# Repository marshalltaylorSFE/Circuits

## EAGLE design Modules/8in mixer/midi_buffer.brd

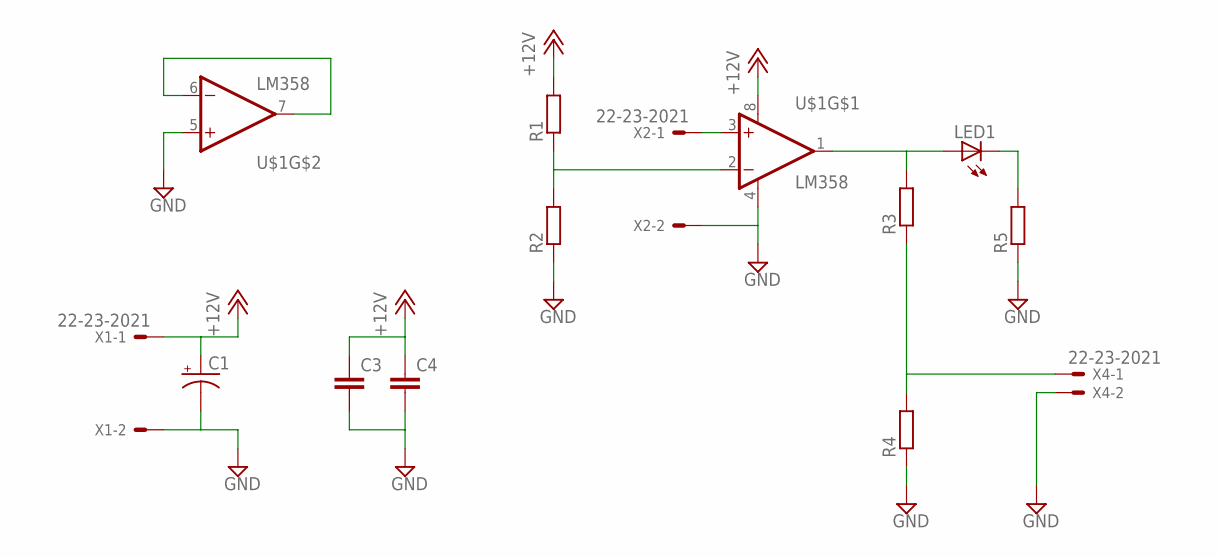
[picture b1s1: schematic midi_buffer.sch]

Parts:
C1: CPOL-USSMCE; SMC_E
C3, C4: C-EUC0603K; C0603K
LED1: LEDSML0805; SML0805
R1, R2, R3, R4, R5: R-EU_R0603; R0603
U$1: LM358; SO08
X1, X2, X4: 22-23-2021

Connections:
+12V: C1.+, C3.1, C4.1, R1.2, U$1.8 (V+), X1.1
GND: C1.-, C3.2, C4.2, R2.1, R4.1, R5.1, U$1.4 (V-), U$1.5 (+IN), X1.2, X2.2, X4.2
unnamed: R3.1, R4.2, X4.1
unnamed: LED1.C, R5.2
unnamed: LED1.A, R3.2, U$1.1 (OUT)
unnamed: R1.1, R2.2, U$1.2 (-IN)
unnamed: U$1.3 (+IN), X2.1
unnamed: U$1.6 (-IN), U$1.7 (OUT)

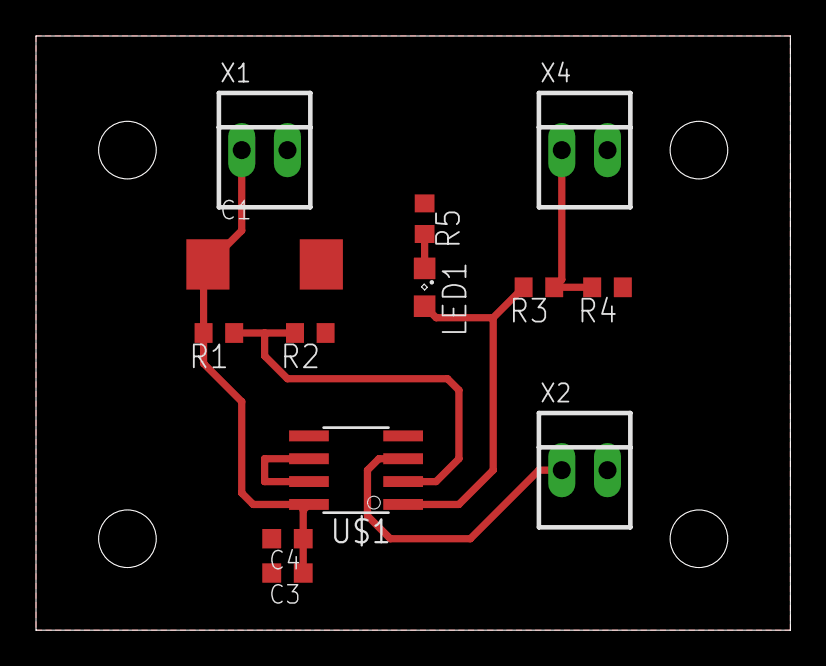
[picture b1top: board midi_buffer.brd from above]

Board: 2 copper layers, 41.9 x 33.0 mm, 13 parts (0 on the bottom side), 8 nets.

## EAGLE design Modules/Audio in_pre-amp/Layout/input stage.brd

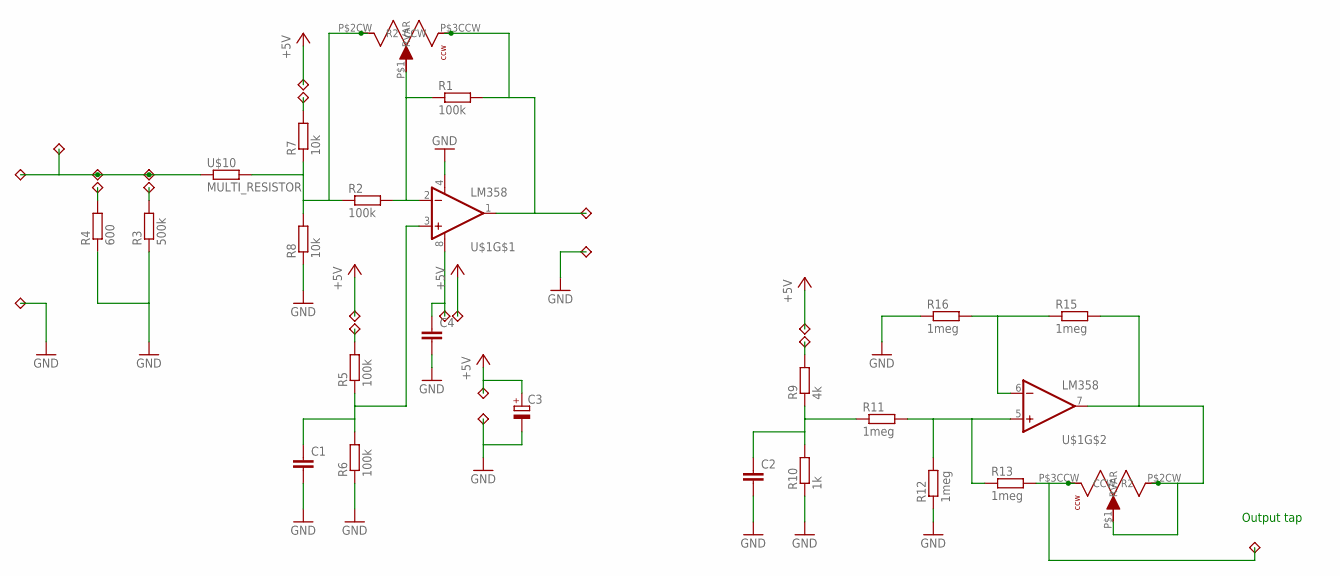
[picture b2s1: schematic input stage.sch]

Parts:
C1, C2, C4: C-EUC0603; C0603
C3: CPOL-EUC/6032-28R; C/6032-28R
R1, R2, R5, R6: 100k; R0603
R3: 500k; R0603
R4: 600; R0603
R7, R8: 10k; R0603
R9: 4k; R0603
R10: 1k; R0603
R11, R12, R13, R15, R16: 1meg; R0603
U$1: LM358; SO08
U$2, U$3, U$4, U$5, U$6, U$7, U$8, U$9, U$11, U$12, U$13, U$14: 1PIN; THUMBNAIL
U$10: MULTI_RESISTOR; MULTI_PAD
U$15, U$24: SMD-POT; POT_PADS
U$16, U$17, U$18, U$19, U$20, U$21, U$22, U$23: 1PIN_SM; THUMBNAIL_SM

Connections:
+5V: C3.+, U$2.P$1, U$17.P$1, U$19.P$1, U$21.P$1, U$23.P$1
GND: C1.2, C2.2, C3.-, C4.2, R3.1, R4.1, R6.1, R8.1, R10.1, R12.1, R16.1, U$1.4 (V-), U$3.P$1, U$8.P$1, U$9.P$1
unnamed: C1.1, R5.1, R6.2, U$1.3 (+IN)
unnamed: R1.1, R2.2, U$1.2 (-IN), U$24.P$1 (RVAR)
unnamed: U$5.P$1, U$6.P$1, U$10.1, U$12.P$1, U$13.P$1
unnamed: R1.2, U$1.1 (OUT), U$4.P$1, U$24.P$3CCW (CCW)
unnamed: R4.2, U$7.P$1
unnamed: R2.1, R7.1, R8.2, U$10.2, U$24.P$2CW (R2)
unnamed: R3.2, U$11.P$1
unnamed: C2.1, R9.1, R10.2, R11.1
unnamed: R15.1, R16.2, U$1.6 (-IN)
unnamed: R15.2, U$1.7 (OUT), U$15.P$1 (RVAR), U$15.P$2CW (R2)
unnamed: R13.2, U$14.P$1, U$15.P$3CCW (CCW)
unnamed: R11.2, R12.2, R13.1, U$1.5 (+IN)
unnamed: R9.2, U$16.P$1
unnamed: R7.2, U$18.P$1
unnamed: R5.2, U$20.P$1
unnamed: C4.1, U$1.8 (V+), U$22.P$1

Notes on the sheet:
Output tap

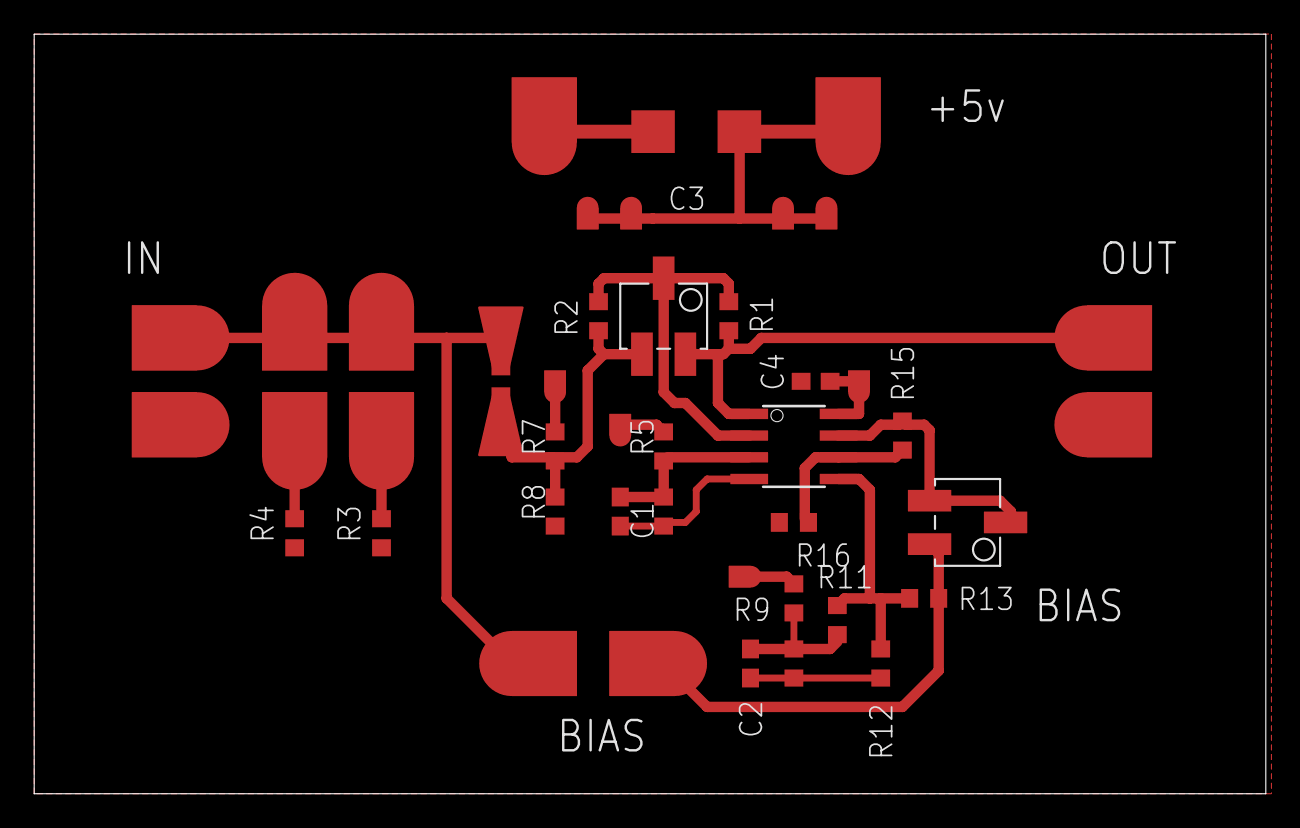
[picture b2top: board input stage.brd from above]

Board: 2 copper layers, 72.1 x 44.4 mm, 43 parts (0 on the bottom side), 18 nets.

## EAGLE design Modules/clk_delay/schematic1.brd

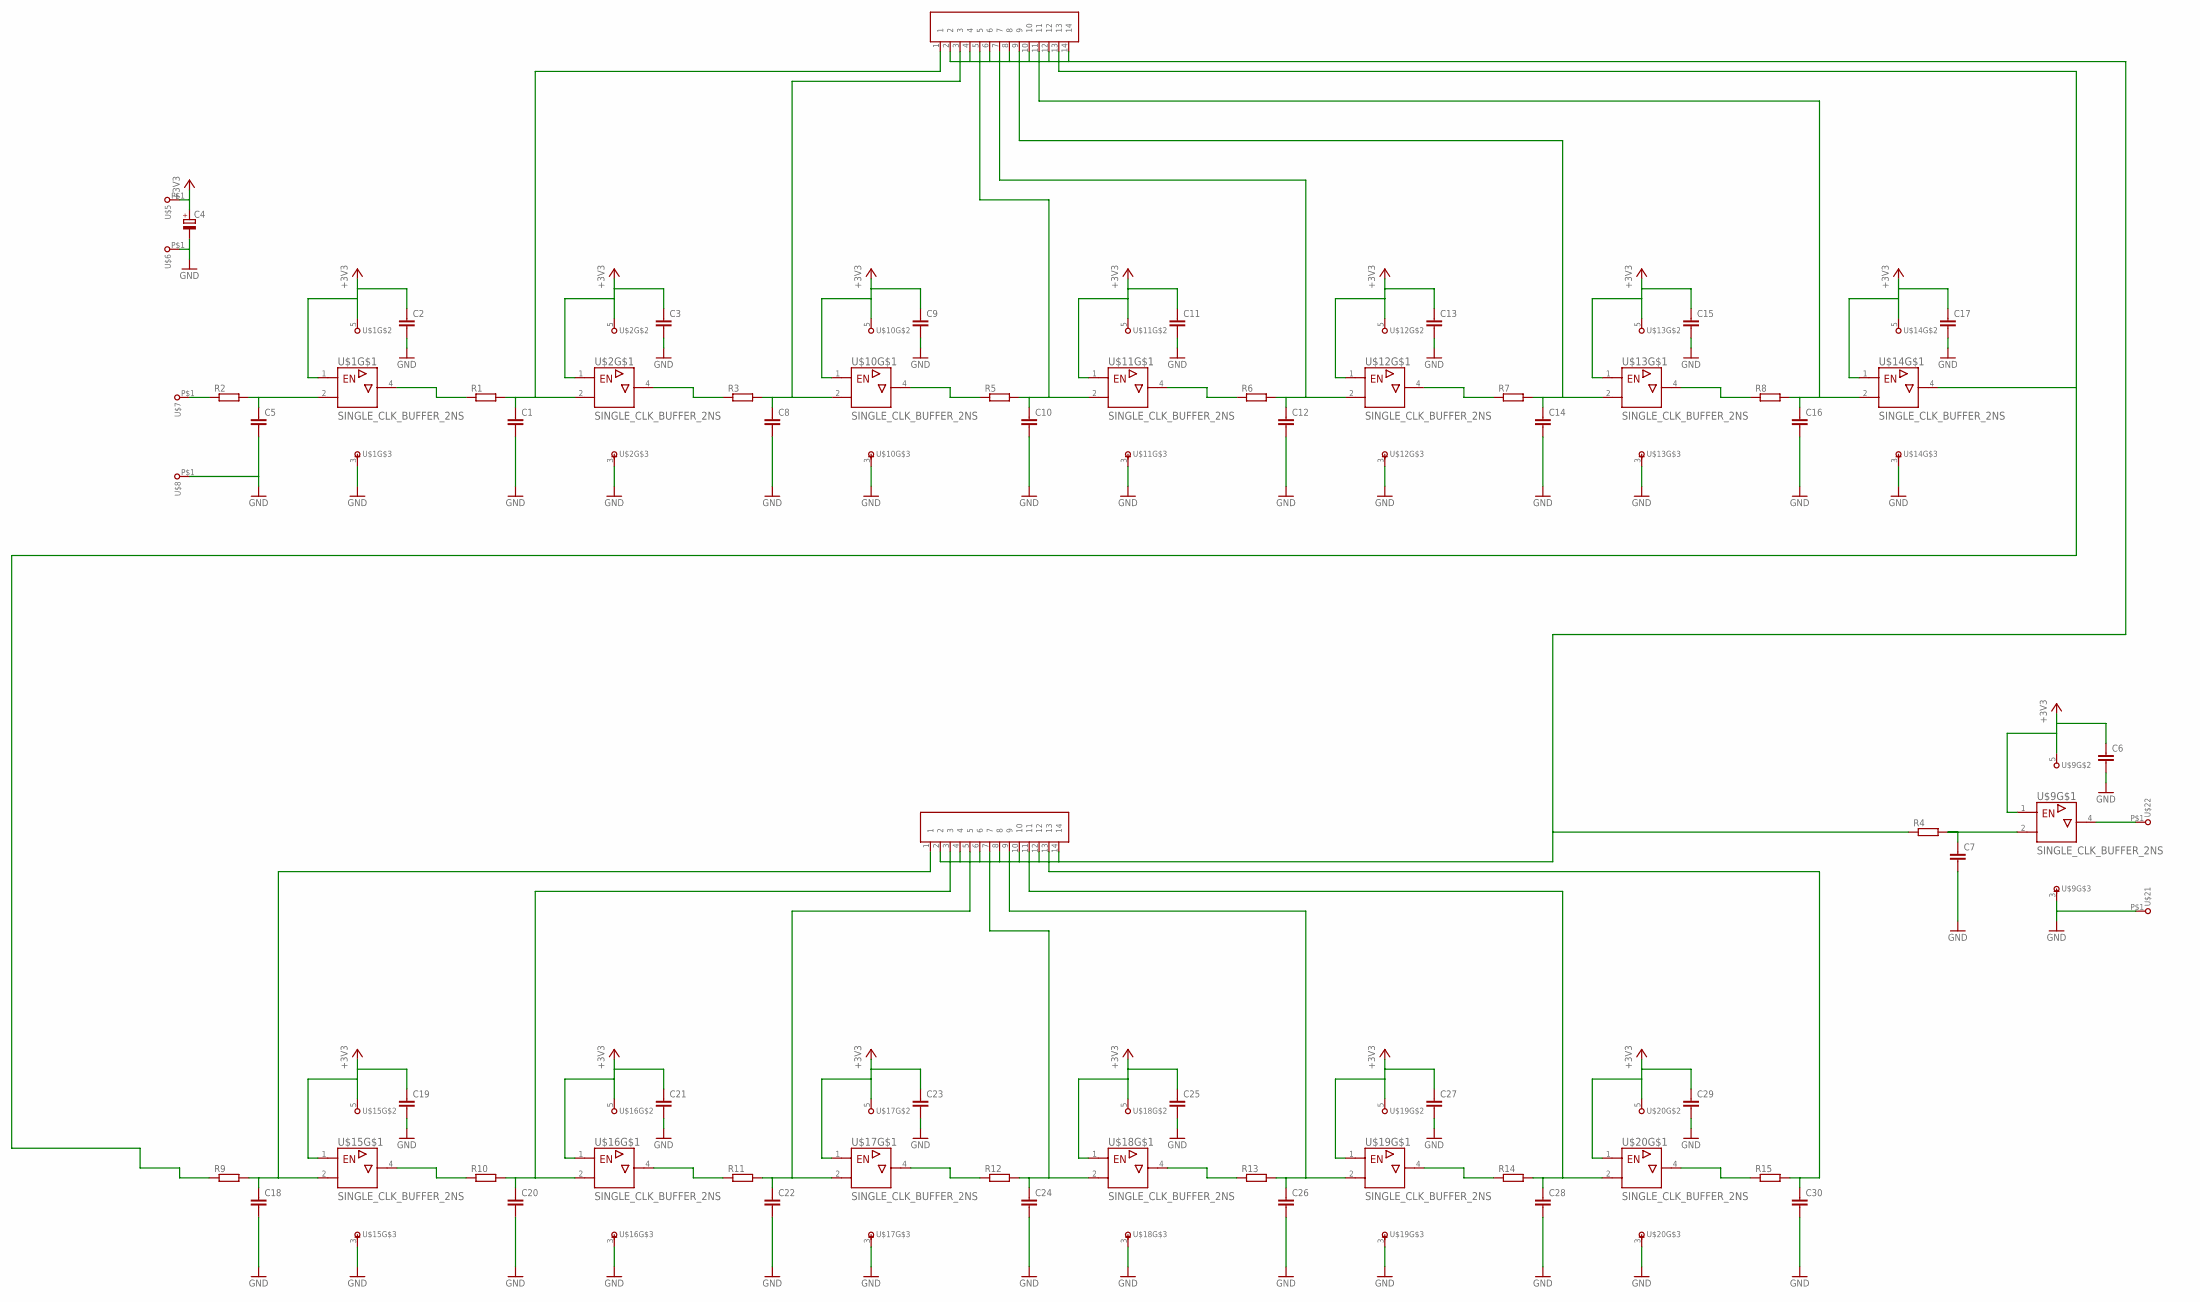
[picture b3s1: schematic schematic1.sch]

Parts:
C1, C5, C7, C8, C10, C12, C14, C16, C18, C20, C22, C24, C26, C28, C30: C-EUC0603; C0603
C2, C3, C6, C9, C11, C13, C15, C17, C19, C21, C23, C25, C27, C29: C-EUC0805; C0805
C4: CPOL-EUSMCD; SMC_D
R1, R2, R3, R4, R5, R6, R7, R8, R9, R10, R11, R12, R13, R14, R15: R-EU_R0603; R0603
U$1, U$2, U$9, U$10, U$11, U$12, U$13, U$14, U$15, U$16, U$17, U$18, U$19, U$20: SINGLE_CLK_BUFFER_2NS; DCK
U$3, U$4: 2X7SMD_HEADER; 2X14SMDPADS
U$5, U$6, U$7, U$8, U$21, U$22: BIGGOPAD

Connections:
+3V3: C2.1, C3.1, C4.+, C6.1, C9.1, C11.1, C13.1, C15.1, C17.1, C19.1, C21.1, C23.1, C25.1, C27.1, C29.1, U$1.1 (G), U$1.5 (+UB), U$2.1 (G), U$2.5 (+UB), U$5.P$1, U$9.1 (G), U$9.5 (+UB), U$10.1 (G), U$10.5 (+UB), U$11.1 (G), U$11.5 (+UB), U$12.1 (G), U$12.5 (+UB), U$13.1 (G), U$13.5 (+UB), U$14.1 (G), U$14.5 (+UB), U$15.1 (G), U$15.5 (+UB), U$16.1 (G), U$16.5 (+UB), U$17.1 (G), U$17.5 (+UB), U$18.1 (G), U$18.5 (+UB), U$19.1 (G), U$19.5 (+UB), U$20.1 (G), U$20.5 (+UB)
GND: C1.2, C2.2, C3.2, C4.-, C5.2, C6.2, C7.2, C8.2, C9.2, C10.2, C11.2, C12.2, C13.2, C14.2, C15.2, C16.2, C17.2, C18.2, C19.2, C20.2, C21.2, C22.2, C23.2, C24.2, C25.2, C26.2, C27.2, C28.2, C29.2, C30.2, U$1.3 (-UB), U$2.3 (-UB), U$6.P$1, U$8.P$1, U$9.3 (-UB), U$10.3 (-UB), U$11.3 (-UB), U$12.3 (-UB), U$13.3 (-UB), U$14.3 (-UB), U$15.3 (-UB), U$16.3 (-UB), U$17.3 (-UB), U$18.3 (-UB), U$19.3 (-UB), U$20.3 (-UB), U$21.P$1
unnamed: C5.1, R2.2, U$1.2 (A)
unnamed: R2.1, U$7.P$1
unnamed: C1.1, R1.2, U$2.2 (A), U$3.1
unnamed: R1.1, U$1.4 (Y)
unnamed: C7.1, R4.2, U$9.2 (A)
unnamed: R3.1, U$2.4 (Y)
unnamed: C8.1, R3.2, U$3.3, U$10.2 (A)
unnamed: C10.1, R5.2, U$3.5, U$11.2 (A)
unnamed: R5.1, U$10.4 (Y)
unnamed: C12.1, R6.2, U$3.7, U$12.2 (A)
unnamed: R6.1, U$11.4 (Y)
unnamed: C14.1, R7.2, U$3.9, U$13.2 (A)
unnamed: R7.1, U$12.4 (Y)
unnamed: C16.1, R8.2, U$3.11, U$14.2 (A)
unnamed: R8.1, U$13.4 (Y)
unnamed: C18.1, R9.2, U$4.1, U$15.2 (A)
unnamed: R9.1, U$3.13, U$14.4 (Y)
unnamed: C20.1, R10.2, U$4.3, U$16.2 (A)
unnamed: R10.1, U$15.4 (Y)
unnamed: C22.1, R11.2, U$4.5, U$17.2 (A)
unnamed: R11.1, U$16.4 (Y)
unnamed: C24.1, R12.2, U$4.7, U$18.2 (A)
unnamed: R12.1, U$17.4 (Y)
unnamed: C26.1, R13.2, U$4.9, U$19.2 (A)
unnamed: R13.1, U$18.4 (Y)
unnamed: C28.1, R14.2, U$4.11, U$20.2 (A)
unnamed: R14.1, U$19.4 (Y)
unnamed: C30.1, R15.2, U$4.13
unnamed: R15.1, U$20.4 (Y)
unnamed: U$9.4 (Y), U$22.P$1
OUTPUT: R4.1, U$3.2, U$3.4, U$3.6, U$3.8, U$3.10, U$3.12, U$3.14, U$4.2, U$4.4, U$4.6, U$4.8, U$4.10, U$4.12, U$4.14

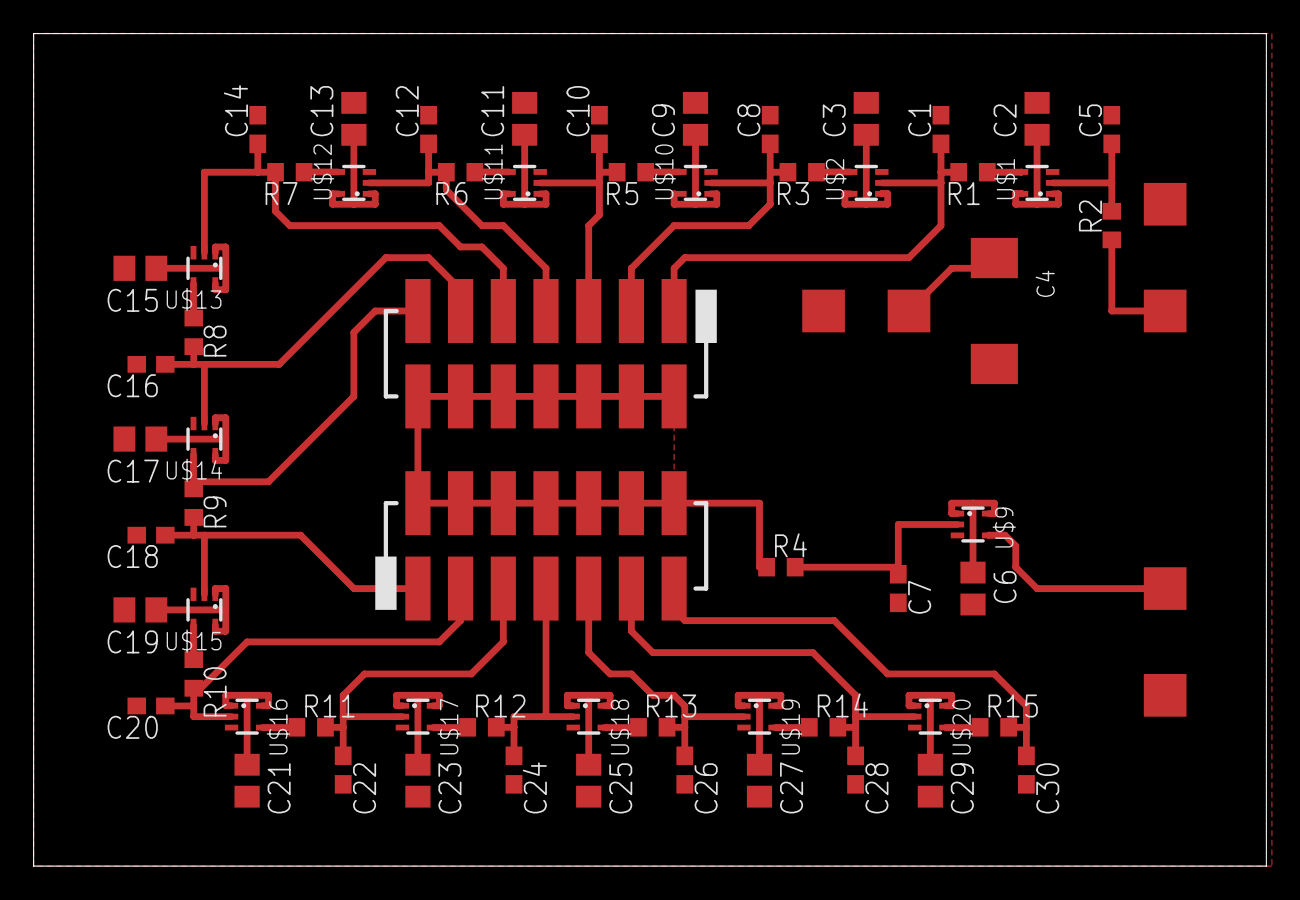
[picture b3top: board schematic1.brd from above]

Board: 2 copper layers, 73.3 x 49.5 mm, 67 parts (0 on the bottom side), 33 nets.
